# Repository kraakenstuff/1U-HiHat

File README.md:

# 1U-HiHat
1U Eurorack hi hat module based on Eric Archer's adaptation of TR808 schematic (http://www.ericarcher.net/wp-content/uploads/2014/07/tr-808-hihat-diy-project-revised-dec-2009.pdf)

Status: never tested.

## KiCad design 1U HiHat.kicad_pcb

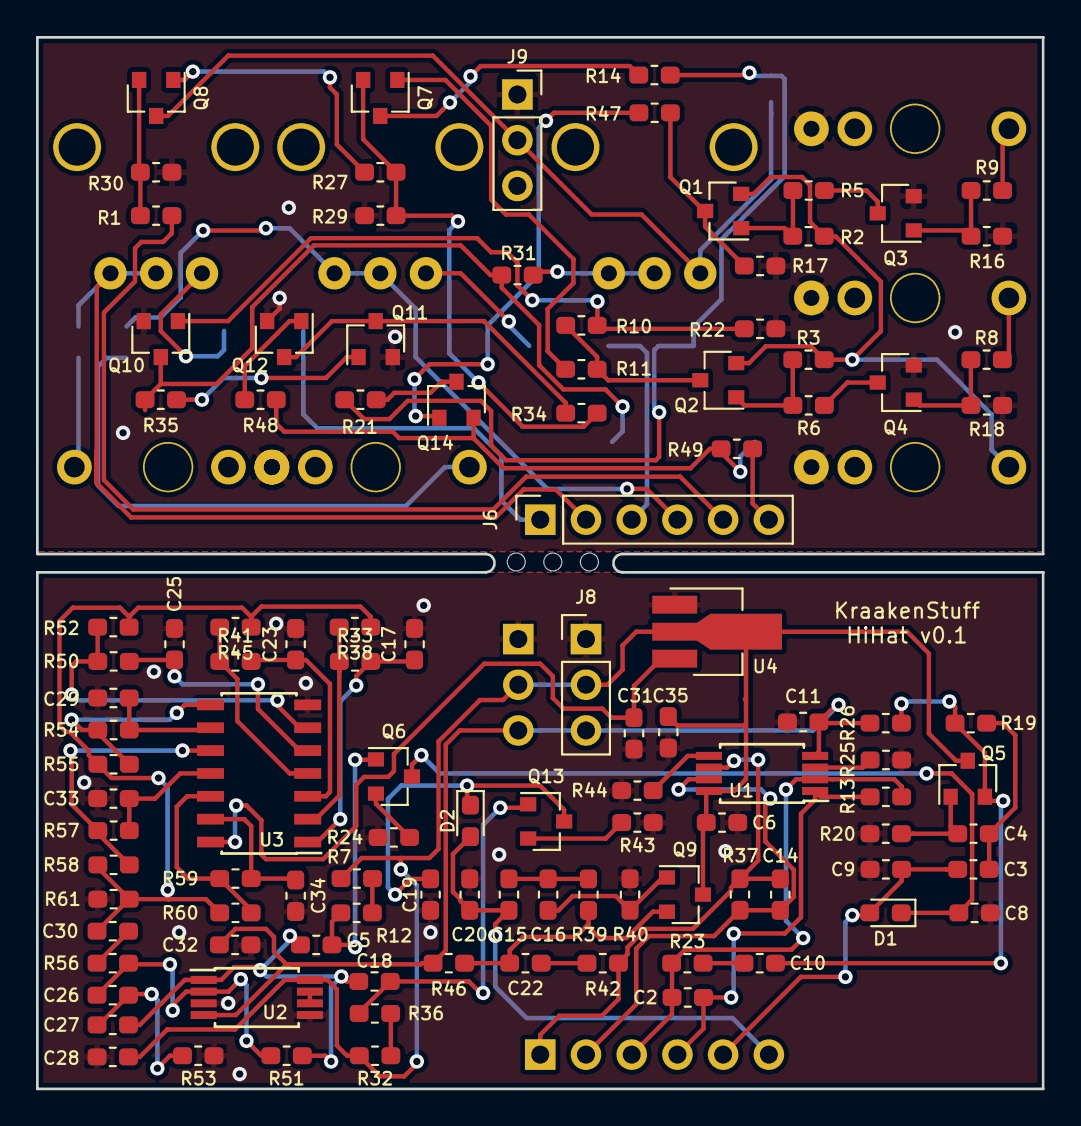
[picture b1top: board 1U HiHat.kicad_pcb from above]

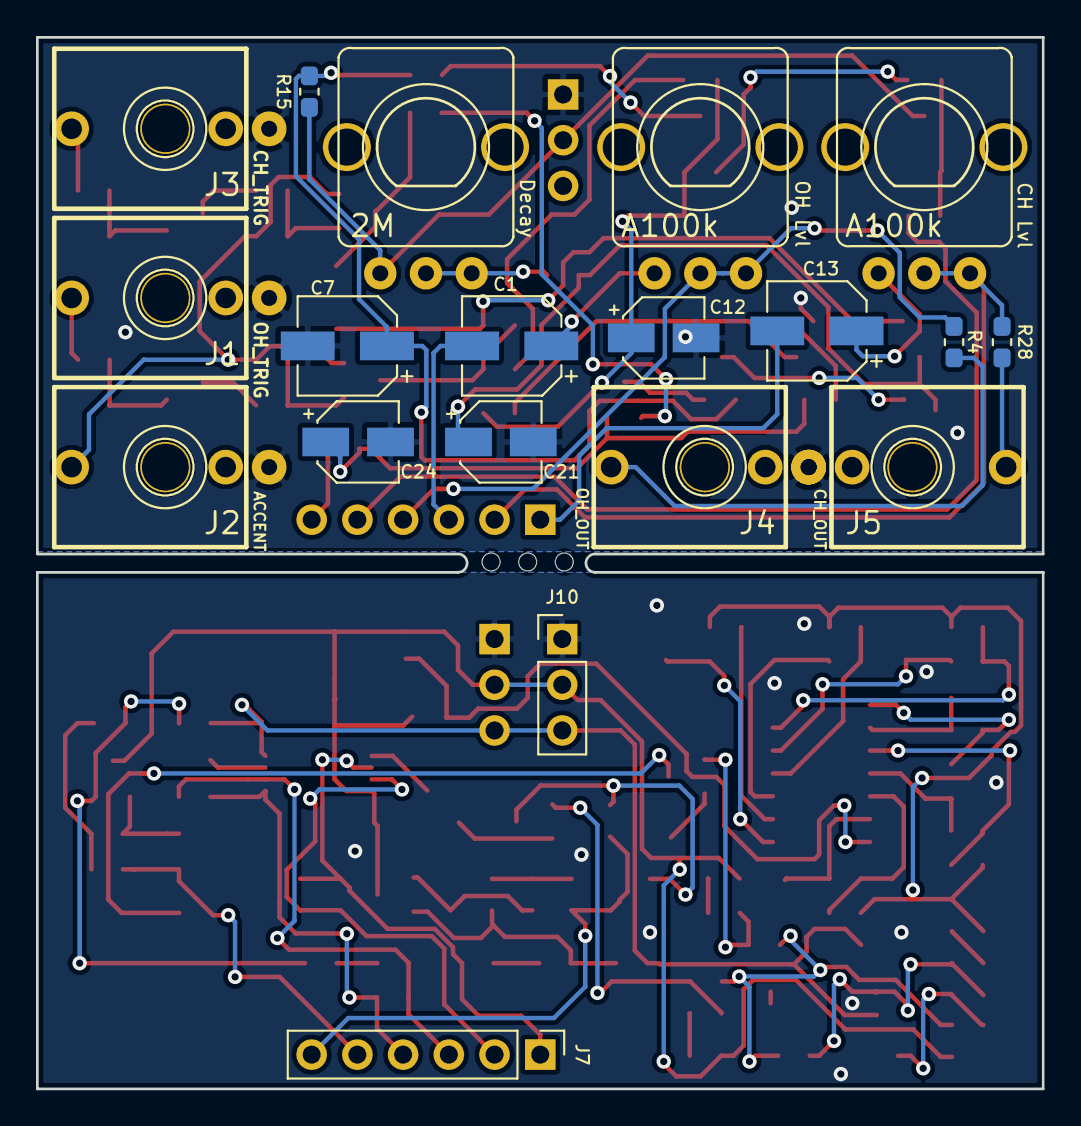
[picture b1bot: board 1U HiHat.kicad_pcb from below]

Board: 2 copper layers, 55.9 x 58.4 mm, 129 parts (19 on the bottom side), 76 nets.

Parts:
C1, C13: 33u; CP_Elec_5x5.8
C2, C14: 220p; C_0603_1608Metric_Pad1.05x0.95mm_HandSolder
C3, C4, C8, C9, C19, C20: 1n5; C_0603_1608Metric_Pad1.05x0.95mm_HandSolder
C5, C17, C18: 22n; C_0603_1608Metric_Pad1.05x0.95mm_HandSolder
C6, C11, C28, C32: 100n; C_0603_1608Metric_Pad1.05x0.95mm_HandSolder
C7: 47u; CP_Elec_5x5.8
C10, C22: 470p; C_0603_1608Metric_Pad1.05x0.95mm_HandSolder
C12, C24: 0.47u; CP_Elec_4x5.8
C15, C16, C30: 1n; C_0603_1608Metric_Pad1.05x0.95mm_HandSolder
C21: 10u; CP_Elec_4x5.8
C23, C25, C34: 18n; C_0603_1608Metric_Pad1.05x0.95mm_HandSolder
C26, C27: 3n3; C_0603_1608Metric_Pad1.05x0.95mm_HandSolder
C29, C33: 10n; C_0603_1608Metric_Pad1.05x0.95mm_HandSolder
C31: 2.2u; C_0603_1608Metric_Pad1.05x0.95mm_HandSolder
C35: 1u; C_0603_1608Metric_Pad1.05x0.95mm_HandSolder
CH Lvl: A100k; POT-9MM-ALPHA
D1, D2: 1N914; D_0603_1608Metric_Pad1.05x0.95mm_HandSolder
Decay: 2M; POT-9MM-ALPHA
J1: OH_TRIG; PJ301M-12
J2: ACCENT; PJ301M-12
J3: CH_TRIG; PJ301M-12
J4: OH_OUT; PJ301M-12
J5: CH_OUT; PJ301M-12
J6: CB; PinSocket_1x06_P2.54mm_Vertical
J7: MB; PinHeader_1x06_P2.54mm_Vertical
J8: PWR; PinHeader_1x03_P2.54mm_Vertical
J9: CB; PinSocket_1x03_P2.54mm_Vertical
J10: MB; PinHeader_1x03_P2.54mm_Vertical
OH Lvl: A100k; POT-9MM-ALPHA
Q1, Q2: BC856; SOT-23
Q3, Q4, Q5, Q6, Q7, Q8, Q9, Q10, Q11, Q12, Q13, Q14: BC846; SOT-23
R1, R27, R30, R42, R47, R49: 33k; R_0603_1608Metric_Pad1.05x0.95mm_HandSolder
R2, R3: 4k7; R_0603_1608Metric_Pad1.05x0.95mm_HandSolder
R4, R28, R61: 1k; R_0603_1608Metric_Pad1.05x0.95mm_HandSolder
R5, R6, R8, R9, R10, R17, R26, R46, R56: 22k; R_0603_1608Metric_Pad1.05x0.95mm_HandSolder
R7, R12, R29, R32, R36: 1M; R_0603_1608Metric_Pad1.05x0.95mm_HandSolder
R11, R16, R18, R22, R35: 10k; R_0603_1608Metric_Pad1.05x0.95mm_HandSolder
R13, R37: 470k; R_0603_1608Metric_Pad1.05x0.95mm_HandSolder
R14, R21: 470; R_0603_1608Metric_Pad1.05x0.95mm_HandSolder
R15, R24, R43: 100; R_0603_1608Metric_Pad1.05x0.95mm_HandSolder
R19, R39: 2k7; R_0603_1608Metric_Pad1.05x0.95mm_HandSolder
R20, R40: 68k; R_0603_1608Metric_Pad1.05x0.95mm_HandSolder
R23: 39k; R_0603_1608Metric_Pad1.05x0.95mm_HandSolder
R25, R44: 47k; R_0603_1608Metric_Pad1.05x0.95mm_HandSolder
R31, R34: 100k; R_0603_1608Metric_Pad1.05x0.95mm_HandSolder
R33: 300k; R_0603_1608Metric_Pad1.05x0.95mm_HandSolder
R38, R45, R52, R55, R58, R60: 120k; R_0603_1608Metric_Pad1.05x0.95mm_HandSolder
R41: 270k; R_0603_1608Metric_Pad1.05x0.95mm_HandSolder
R48: 330k; R_0603_1608Metric_Pad1.05x0.95mm_HandSolder
R50: 220k; R_0603_1608Metric_Pad1.05x0.95mm_HandSolder
R51: 82k; R_0603_1608Metric_Pad1.05x0.95mm_HandSolder
R53: 560; R_0603_1608Metric_Pad1.05x0.95mm_HandSolder
R54: 680k; R_0603_1608Metric_Pad1.05x0.95mm_HandSolder
R57, R59: 560k; R_0603_1608Metric_Pad1.05x0.95mm_HandSolder
U1, U2: TL072; TSSOP-8_4.4x3mm_P0.65mm
U3: 4584; SOIC-14_3.9x8.7mm_P1.27mm
U4: AP7380-50Y-13; SOT-89-3_Handsoldering

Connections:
+5V: C31.2, U3.14, U4.3
+12V: C6.1, C28.2, C35.2, Decay.1, J8.2, J9.2, J10.2, Q5.3, Q8.3, Q9.3, R7.1, R15.1, R32.1, U1.8, U2.8, U4.2
-12V: C11.2, C32.1, J8.3, J9.3, J10.3, R26.2, R46.2, U1.4, U2.4
CH_LVL1: C13.2, C14.1, J6.1, J7.1, R37.2, R42.1, U1.6
CH_LVL2: C14.2, CH Lvl.2, CH Lvl.3, J6.2, J7.2, R28.1, R37.1, U1.7
GND: C6.2, C7.2, C8.1, C9.1, C11.1, C12.2, C17.2, C19.1, C20.1, C21.2, C23.2, C24.2, C25.2, C28.1, C29.2, C31.1, C32.2, C33.2, C34.2, C35.1, J1.S, J2.S, J3.S, J4.S, J5.S, J8.1, J9.1, J10.1, Q3.2, Q4.2, Q10.2, Q11.2, Q12.2, R16.2, R17.2, R18.2, R20.2, R22.2, R24.2, R25.2, R29.1, R30.1, R40.2, R43.2, R44.2, R53.1, R61.1, U2.3, U2.5, U3.7, U4.1
NOISE: C5.2, C18.2, C27.1, R51.1, U2.1
unnamed: C1.1, OH Lvl.1
unnamed: C3.2, C4.1, R19.1
unnamed: C4.2, Q5.1, R20.1
unnamed: C5.1, Q6.1, R12.2
unnamed: C7.1, R14.1, R15.2, R21.1
unnamed: C8.2, D1.1, Q6.3
unnamed: C10.1, Q5.2, R19.2, R26.1
unnamed: C10.2, R23.2
unnamed: C12.1, Q7.2, R27.2, R29.2, R34.2
unnamed: C13.1, CH Lvl.1
unnamed: C15.2, C16.1, R39.1
unnamed: C16.2, Q9.1, R40.1
unnamed: C17.1, R33.2, U3.1
unnamed: C18.1, Q13.1, R36.2
unnamed: C19.2, D2.1, Q13.3
unnamed: C21.1, Q10.3, R31.1, R35.2
unnamed: C22.1, Q9.2, R39.2, R46.1
unnamed: C22.2, R42.2
unnamed: C23.1, R41.2, U3.3
unnamed: C24.1, Q14.2, R48.1, R49.2
unnamed: C25.1, R50.2, U3.5
unnamed: C26.1, C27.2, R53.2
unnamed: C26.2, R51.2, R56.1, U2.2
unnamed: C29.1, R54.2, U3.9
unnamed: C30.1, R56.2
unnamed: C30.2, R38.1, R45.1, R52.1, R55.1, R58.1, R60.1, R61.2
unnamed: C33.1, R57.2, U3.11
unnamed: C34.1, R59.2, U3.13
unnamed: J1.T, R8.1
unnamed: J2.T, Q1.2, Q2.2, R2.1, R3.1
unnamed: J3.T, R9.1
unnamed: J4.T, R4.2
unnamed: J5.T, R28.2
unnamed: Decay.2, Decay.3, R31.2
unnamed: Q1.1, R2.2, R5.1
unnamed: Q1.3, R17.1, R47.2
unnamed: Q2.1, R3.2, R6.1
unnamed: Q2.3, R10.1, R11.1
unnamed: Q3.1, R9.2, R16.1
unnamed: Q3.3, R5.2
unnamed: Q4.1, R8.2, R18.1
unnamed: Q4.3, R6.2
unnamed: Q6.2, R24.1
unnamed: Q7.1, R11.2
unnamed: Q7.3, R14.2
unnamed: Q8.1, R27.1
unnamed: Q8.2, R1.2, R30.2
unnamed: Q10.1, R10.2, R22.1
unnamed: Q11.1, R35.1
unnamed: Q11.3, Q12.3, R34.1
unnamed: Q12.1, R48.2
unnamed: Q13.2, R43.1
unnamed: Q14.1, R47.1
unnamed: Q14.3, R21.2
unnamed: R7.2, R12.1
unnamed: R25.1, U1.3
unnamed: R32.2, R36.1
unnamed: R33.1, R38.2, U3.2
unnamed: R41.1, R45.2, U3.4
unnamed: R44.1, U1.5
unnamed: R50.1, R52.2, U3.6
unnamed: R54.1, R55.2, U3.8
unnamed: R57.1, R58.2, U3.10
unnamed: R59.1, R60.2, U3.12
unnamed: U2.6, U2.7
OH_LVL1: C1.2, C2.1, J6.3, J7.3, R13.2, R23.1, U1.2
OH_LVL2: C2.2, J6.4, J7.4, OH Lvl.2, OH Lvl.3, R4.1, R13.1, U1.1
TO_CH: C15.1, C20.2, D2.2, J6.6, J7.6, R49.1
TO_OH: C3.1, C9.2, D1.2, J6.5, J7.5, R1.1

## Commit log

2019-01-07 Complete redesign started
2019-01-07 Half of the main board done. Fixed errors in schematics. Added 3D pots
2019-01-08 Finished main board
2019-01-08 Finished v0.1
